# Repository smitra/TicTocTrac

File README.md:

TicTocTrac
==========

TicTocTrac is a watch designed as part of ECE4760 at Cornell University that allows you to not only keep time, but track your perception of it. Learn what causes time to slow down or speed up!

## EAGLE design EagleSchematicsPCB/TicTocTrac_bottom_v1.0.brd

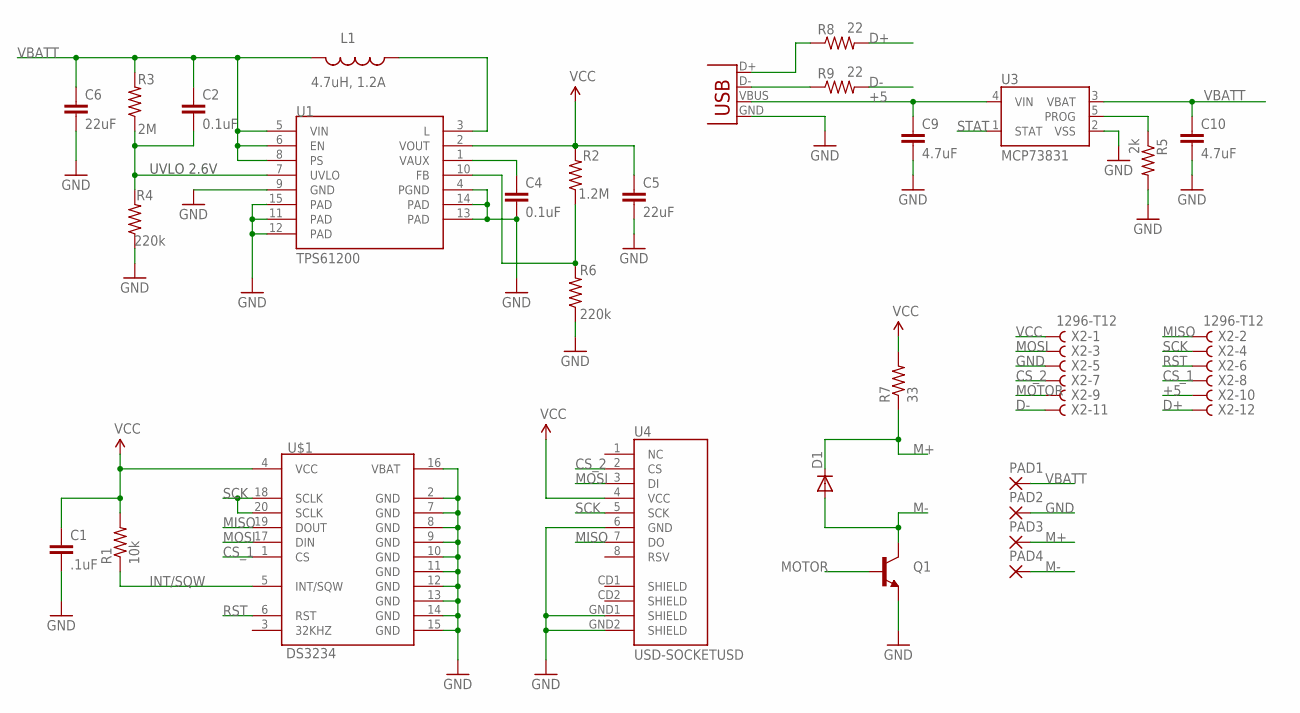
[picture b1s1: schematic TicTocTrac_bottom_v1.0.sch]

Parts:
C1: .1uF; 0402-CAP
C2, C4: 0.1uF; 0402-CAP
C5, C6: 22uF; 0805
C9, C10: 4.7uF; 0402-CAP
D1: DIODESOD; SOD-323
L1: 4.7uH, 1.2A; CDRH2D09
PAD1, PAD2, PAD3, PAD4: 1,6/0,8
Q1: TRANSISTOR_NPNSOT23; SOT23
R1: 10k; 0402-RES
R2: 1.2M; 0402-RES
R3: 2M; 0402-RES
R4, R6: 220k; 0402-RES
R5: 2k; 0402-RES
R7: 33; 0805
R8, R9: 22; 0402-RES
U1: TPS61200; QFN-10_PAD
U3: MCP73831; SOT23-5
U4: USD-SOCKETUSD; USD-SOCKET-PP
U$1: DS3234
X1: USB-MICROB
X2: 1296-T12; 1296-12

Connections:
3.3V: R2.1, R6.2, U1.10 (FB)
+5: C9.1, U3.4 (VIN), X1.VBUS, X2.10
CS_1: U$1.1 (CS), X2.8
CS_2: U4.2 (CS), X2.7
D+: R8.2, X2.12
D-: R9.2, X2.11
GND: C1.2, C4.2, C5.2, C6.2, C9.2, C10.2, PAD2.1, Q1.2 (E), R4.1, R5.2, R6.1, U1.4 (PGND), U1.11 (PAD), U1.12 (PAD), U1.13 (PAD), U1.14 (PAD), U1.15 (PAD), U3.2 (VSS), U4.6 (GND), U4.GND1 (SHIELD), U4.GND2 (SHIELD), U$1.2 (GND), U$1.7 (GND), U$1.8 (GND), U$1.9 (GND), U$1.10 (GND), U$1.11 (GND), U$1.12 (GND), U$1.13 (GND), U$1.14 (GND), U$1.15 (GND), U$1.16 (VBAT), X1.GND, X2.5
INT/SQW: R1.1, U$1.5 (INT/SQW)
M+: D1.1 (C), PAD3.1, R7.1
M-: D1.2 (A), PAD4.1, Q1.3 (C)
MISO: U4.7 (DO), U$1.19 (DOUT), X2.2
MOSI: U4.3 (DI), U$1.17 (DIN), X2.3
MOTOR: Q1.1 (B), X2.9
unnamed: C4.1, U1.1 (VAUX)
unnamed: L1.P$1 (1), U1.3 (L)
unnamed: R9.1, X1.D-
unnamed: R8.1, X1.D+
unnamed: R5.1, U3.5 (PROG)
RST: U$1.6 (RST), X2.6
SCK: U4.5 (SCK), U$1.18 (SCLK), U$1.20 (SCLK), X2.4
STAT: U3.1 (STAT)
UVLO: C2.2, R3.1, R4.2, U1.7 (UVLO)
VBATT: C2.1, C6.1, C10.1, L1.P$2 (2), PAD1.1, R3.2, U1.5 (VIN), U1.6 (EN), U1.8 (PS), U3.3 (VBAT)
VCC: C1.1, C5.1, R1.2, R2.2, R7.2, U1.2 (VOUT), U4.4 (VCC), U$1.4 (VCC), X2.1

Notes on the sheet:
UVLO 2.6V

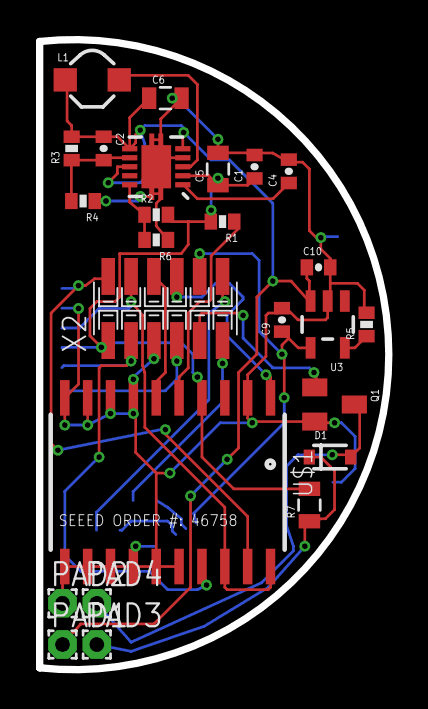
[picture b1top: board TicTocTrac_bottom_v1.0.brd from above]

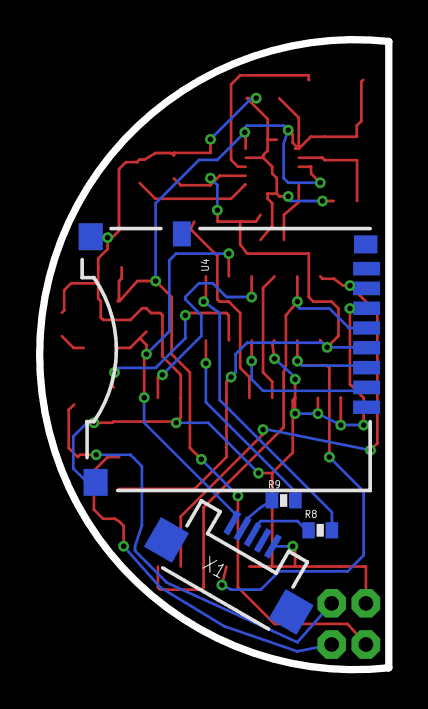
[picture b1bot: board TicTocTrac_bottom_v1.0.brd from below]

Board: 2 copper layers, 19.4 x 35.0 mm, 29 parts (4 on the bottom side), 23 nets.

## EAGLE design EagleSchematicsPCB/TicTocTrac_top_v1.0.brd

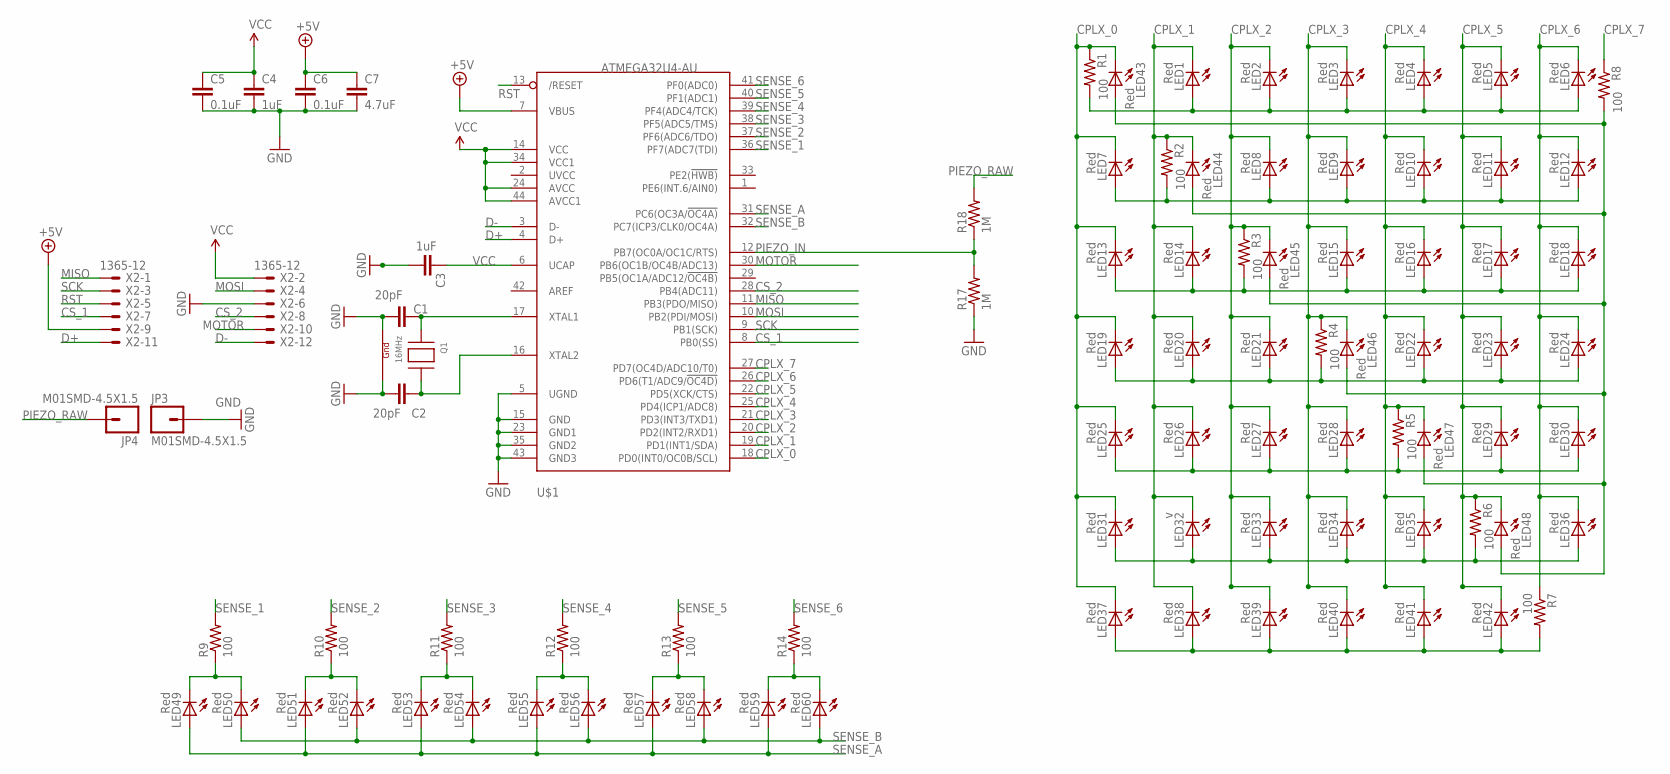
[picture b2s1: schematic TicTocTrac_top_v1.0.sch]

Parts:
C1, C2: 20pF; 0402-CAP
C3, C4: 1uF; 0402-CAP
C5, C6: 0.1uF; 0402-CAP
C7: 4.7uF; 0402-CAP
JP3, JP4: M01SMD-4.5X1.5; PAD-1.5X4.5
LED1, LED2, LED3, LED4, LED5, LED6, LED7, LED8, LED9, LED10, LED11, LED12, LED13, LED14, LED15, LED16, LED17, LED18, LED19, LED20, LED21, LED22, LED23, LED24, LED25, LED26, LED27, LED28, LED29, LED30, LED31, LED33, LED34, LED35, LED36, LED37, LED38, LED39, LED40, LED41, LED42, LED43, LED44, LED45, LED46, LED47, LED48, LED49, LED50, LED51, LED52, LED53, LED54, LED55, LED56, LED57, LED58, LED59, LED60: Red; LED-0603
LED32: v; LED-0603
Q1: 16MHz; NX3225
R1, R2, R3, R4, R5, R6, R7, R8, R9, R10, R11, R12, R13, R14: 100; 0402-RES
R17, R18: 1M; 0805
U$1: ATMEGA32U4-AU; TQFP44
X2: 1365-12

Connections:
+5V: C6.1, C7.1, U$1.7 (VBUS), X2.9
CPLX_0: LED7.C, LED13.C, LED19.C, LED25.C, LED31.C, LED37.C, LED43.C, R1.1, U$1.18 (PD0(INT0/OC0B/SCL))
CPLX_1: LED1.C, LED14.C, LED20.C, LED26.C, LED32.C, LED38.C, LED44.C, R2.1, U$1.19 (PD1(INT1/SDA))
CPLX_2: LED2.C, LED8.C, LED21.C, LED27.C, LED33.C, LED39.C, LED45.C, R3.1, U$1.20 (PD2(INT2/RXD1))
CPLX_3: LED3.C, LED9.C, LED15.C, LED28.C, LED34.C, LED40.C, LED46.C, R4.1, U$1.21 (PD3(INT3/TXD1))
CPLX_4: LED4.C, LED10.C, LED16.C, LED22.C, LED35.C, LED41.C, LED47.C, R5.1, U$1.25 (PD4(ICP1/ADC8))
CPLX_5: LED5.C, LED11.C, LED17.C, LED23.C, LED29.C, LED42.C, LED48.C, R6.1, U$1.22 (PD5(XCK/CTS))
CPLX_6: LED6.C, LED12.C, LED18.C, LED24.C, LED30.C, LED36.C, R7.1, U$1.26 (PD6(T1/ADC9/!OC4D))
CPLX_7: R8.1, U$1.27 (PD7(OC4D/ADC10/T0))
CS_1: U$1.8 (PB0(SS)), X2.7
CS_2: U$1.28 (PB4(ADC11)), X2.8
D+: U$1.4 (D+), X2.11
D-: U$1.3 (D-), X2.12
GND: C1.2, C2.2, C3.2, C4.2, C5.2, C6.2, C7.2, JP3.P$1, Q1.2 (G2), Q1.4 (G1), R17.1, U$1.5 (UGND), U$1.15 (GND), U$1.23 (GND1), U$1.35 (GND2), U$1.43 (GND3), X2.6
MISO: U$1.11 (PB3(PDO/MISO)), X2.1
MOSI: U$1.10 (PB2(PDI/MOSI)), X2.4
MOTOR: U$1.30 (PB6(OC1B/OC4B/ADC13)), X2.10
unnamed: C2.1, Q1.3 (X2), U$1.16 (XTAL2)
unnamed: C1.1, Q1.1 (X1), U$1.17 (XTAL1)
unnamed: LED19.A, LED20.A, LED21.A, LED22.A, LED23.A, LED24.A, R4.2
unnamed: LED1.A, LED2.A, LED3.A, LED4.A, LED5.A, LED6.A, R1.2
unnamed: LED7.A, LED8.A, LED9.A, LED10.A, LED11.A, LED12.A, R2.2
unnamed: LED25.A, LED26.A, LED27.A, LED28.A, LED29.A, LED30.A, R5.2
unnamed: LED13.A, LED14.A, LED15.A, LED16.A, LED17.A, LED18.A, R3.2
unnamed: LED43.A, LED44.A, LED45.A, LED46.A, LED47.A, LED48.A, R8.2
unnamed: LED37.A, LED38.A, LED39.A, LED40.A, LED41.A, LED42.A, R7.2
unnamed: LED31.A, LED32.A, LED33.A, LED34.A, LED35.A, LED36.A, R6.2
unnamed: LED49.C, LED50.C, R9.1
unnamed: LED51.C, LED52.C, R10.1
unnamed: LED53.C, LED54.C, R11.1
unnamed: LED55.C, LED56.C, R12.1
unnamed: LED57.C, LED58.C, R13.1
unnamed: LED59.C, LED60.C, R14.1
PIEZO_IN: R17.2, R18.1, U$1.12 (PB7(OC0A/OC1C/RTS))
PIEZO_RAW: JP4.P$1, R18.2
RST: U$1.13 (/RESET), X2.5
SCK: U$1.9 (PB1(SCK)), X2.3
SENSE_1: R9.2, U$1.36 (PF7(ADC7(TDI))
SENSE_2: R10.2, U$1.37 (PF6(ADC6/TDO))
SENSE_3: R11.2, U$1.38 (PF5(ADC5/TMS))
SENSE_4: R12.2, U$1.39 (PF4(ADC4/TCK))
SENSE_5: R13.2, U$1.40 (PF1(ADC1))
SENSE_6: R14.2, U$1.41 (PF0(ADC0))
SENSE_A: LED49.A, LED51.A, LED53.A, LED55.A, LED57.A, LED59.A, U$1.31 (PC6(OC3A/!OC4A))
SENSE_B: LED50.A, LED52.A, LED54.A, LED56.A, LED58.A, LED60.A, U$1.32 (PC7(ICP3/CLK0/OC4A))
VCC: C3.1, C4.1, C5.1, U$1.6 (UCAP), U$1.14 (VCC), U$1.24 (AVCC), U$1.34 (VCC1), U$1.44 (AVCC1), X2.2

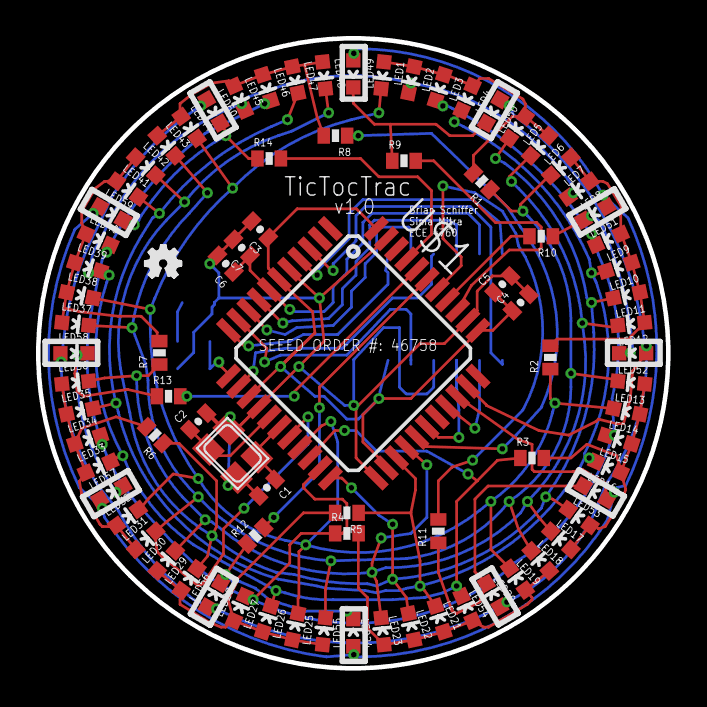
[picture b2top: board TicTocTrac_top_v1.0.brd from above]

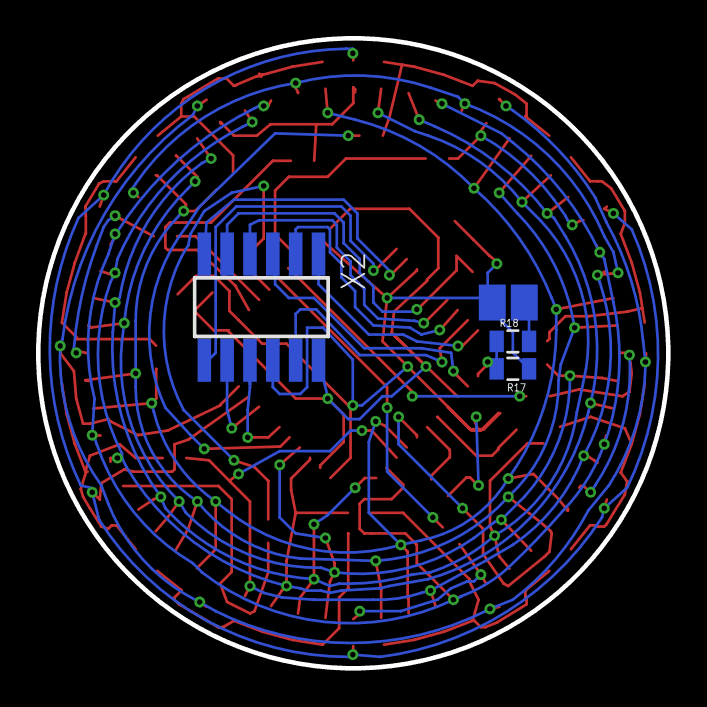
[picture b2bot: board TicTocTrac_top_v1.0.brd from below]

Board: 2 copper layers, 35.0 x 35.0 mm, 89 parts (5 on the bottom side), 46 nets.

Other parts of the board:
U$2: OSHW_FILLX70_NOTEXT

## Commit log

2012-05-03 Added README
2012-05-03 Updating github
2012-05-03 Removing old readme.md
2012-05-03 Added TicTocTrac v1.0 including: -Eagle Files -C code -3D case -SD card bootloader

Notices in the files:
parts and their libraries:
SparkFun: Licensing: CC v3.0 Share-Alike You are welcome to use this library for commercial purposes.
